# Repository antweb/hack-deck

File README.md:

# Hack Deck

A simple macro keyboard designed from scratch.

## Overview

### Microcontroller
Raspberry Pi Pico running a simple CircuitPython firmware that acts as a USB HID keyboard.

### PCB
The board offers room for eight Cherry MX compatible switches. Each switch is wired to its own GPIO port on the Pico and all share one common ground connector.

### Case
Simple enclosure consisting of a top and bottom half.

## Part List
Other than the board and the case that can be produced from the designs, following parts are needed:
* 1x Raspberry Pi Pico
* 2x 20 pin short female header
* 8x Cherry MX compatible switch
* 8x Cherry MX compatible keycap
* 4x M3x10 screw
* 4x M3 nut

Keyswitches with fixing pins are recommended (e.g. Cherry MX1A-E1NN), as they make it easier to solder them to the PCB. For switches without fixing pins, the soldering aid included in the case designs can be used to align things evenly.

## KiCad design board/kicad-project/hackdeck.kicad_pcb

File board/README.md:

# PCB
Circuit board design to hold and connect eight keyboard switches and a Raspberry Pi Pico.

Created with KiCad 5.1.10 using [this template](https://github.com/sethhillbrand/kicad_templates/tree/master/AISLER-2Layer).

### Footprints
The design uses additional footprint libraries:
* [RP_Silicon_KiCad](https://github.com/HeadBoffin/RP_Silicon_KiCad)
* [Button_Switch_Keyboard.pretty](https://gitlab.com/kicad/libraries/kicad-footprints/-/tree/master/Button_Switch_Keyboard.pretty)

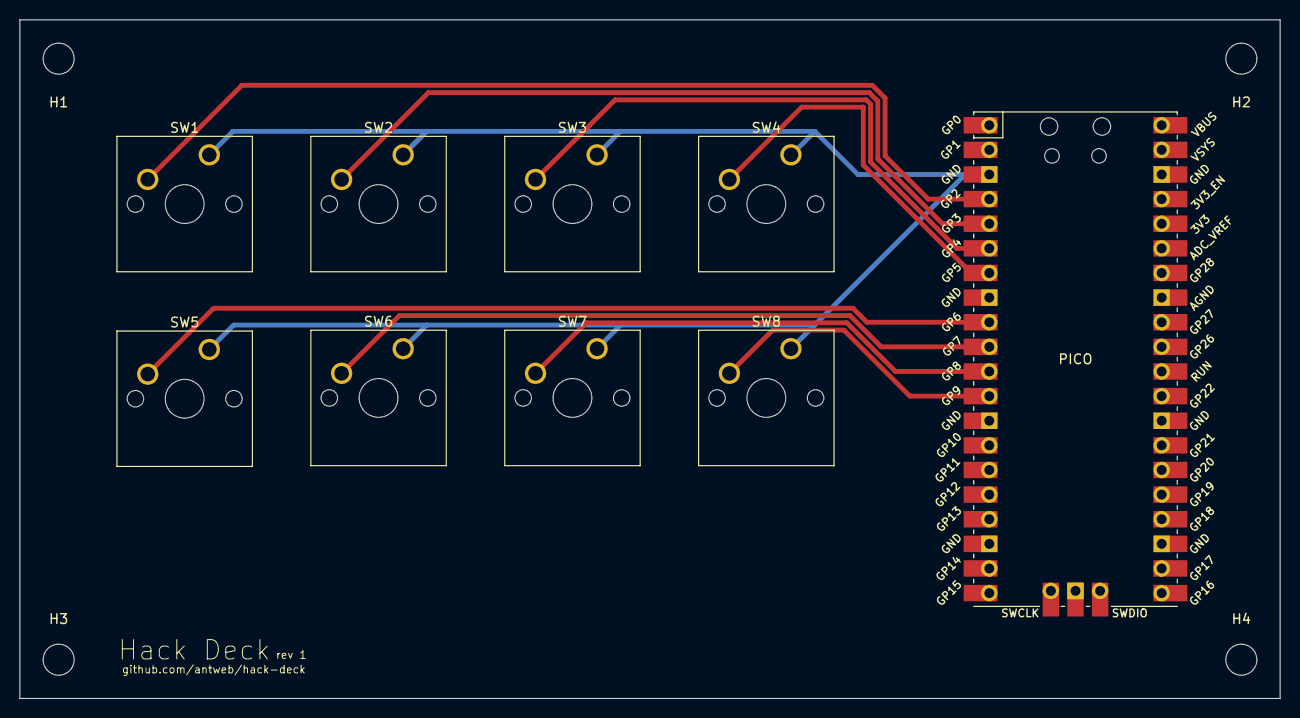
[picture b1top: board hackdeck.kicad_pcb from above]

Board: 2 copper layers, 130.0 x 70.0 mm, 13 parts (0 on the bottom side), 9 nets.

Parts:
H1, H2, H3, H4: MountingHole; MountingHole_3.2mm_M3
PICO: Pico; RPi_Pico_SMD_TH
SW1: Button 1; SW_Cherry_MX_1.00u_PCB
SW2: Button 2; SW_Cherry_MX_1.00u_PCB
SW3: Button 3; SW_Cherry_MX_1.00u_PCB
SW4: Button 4; SW_Cherry_MX_1.00u_PCB
SW5: Button 5; SW_Cherry_MX_1.00u_PCB
SW6: Button 6; SW_Cherry_MX_1.00u_PCB
SW7: Button 7; SW_Cherry_MX_1.00u_PCB
SW8: Button 8; SW_Cherry_MX_1.00u_PCB

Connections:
GND: PICO.3, SW1.1, SW2.1, SW3.1, SW4.1, SW5.1, SW6.1, SW7.1, SW8.1
unnamed: PICO.4, SW1.2
unnamed: PICO.5, SW2.2
unnamed: PICO.6, SW3.2
unnamed: PICO.7, SW4.2
unnamed: PICO.9, SW5.2
unnamed: PICO.10, SW6.2
unnamed: PICO.11, SW7.2
unnamed: PICO.12, SW8.2

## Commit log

2021-05-06 add readme
2021-05-06 add firmware license
2021-05-06 document firmware
2021-05-06 add firmware source code
2021-05-06 add license for case parts
2021-05-06 add case designs
2021-05-06 add design for solder aid
2021-05-06 document case designs
2021-05-24 add license for board design
2021-05-24 document board design
2021-05-24 add board designs
2021-05-24 add photo to main readme
2021-05-24 add case design images
2021-05-24 add screenshot of board design
2021-05-24 add image of soldering aid
2021-05-24 document part list
